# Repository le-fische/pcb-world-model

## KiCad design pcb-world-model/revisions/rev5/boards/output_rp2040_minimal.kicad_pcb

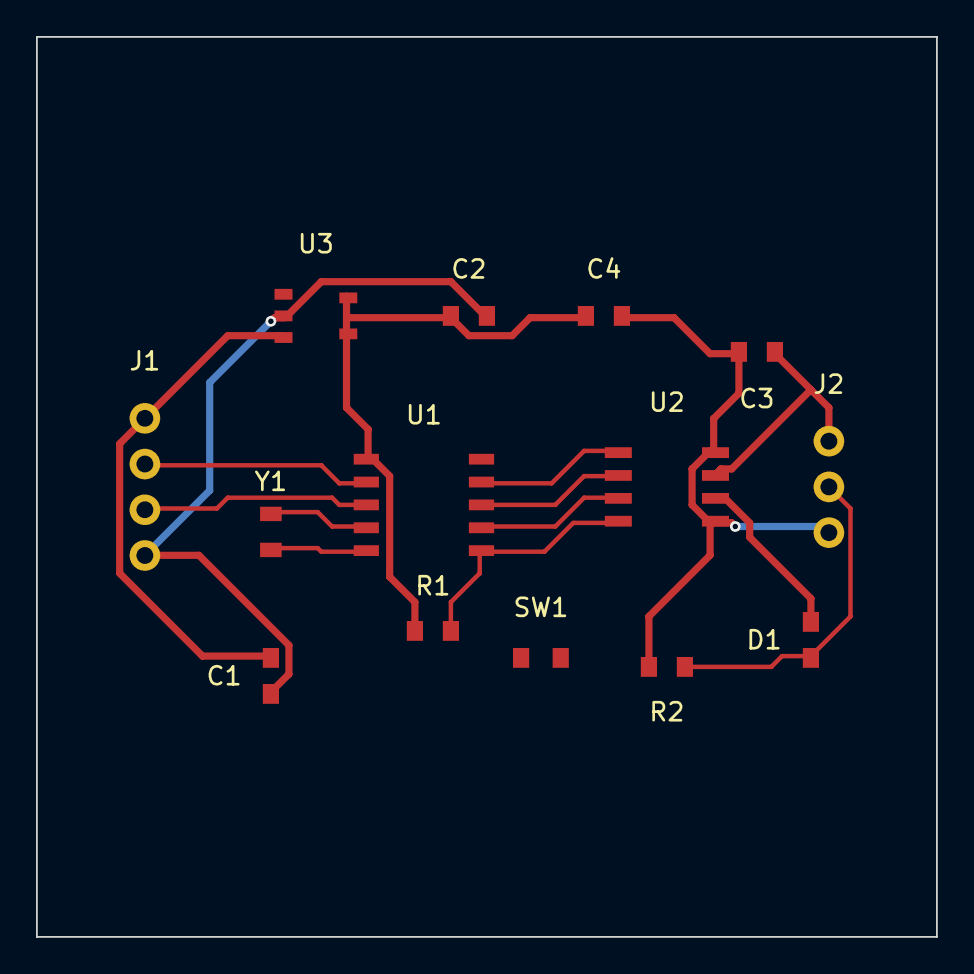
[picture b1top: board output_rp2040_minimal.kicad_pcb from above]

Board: 2 copper layers, 50.0 x 50.0 mm, 14 parts (0 on the bottom side), 12 nets.

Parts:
C1: 10uF_VBUS; C_0805_2012Metric
C2: 100nF_VDD; C_0805_2012Metric
C3: 100nF_CORE; C_0805_2012Metric
C4: 100nF_FLASH; C_0805_2012Metric
D1: PWR_LED; LED_0805_2012Metric
J1: USB_C; USB_C_Receptacle_GCT_USB4085
J2: GPIO_HDR; PinHeader_1x03_P2.54mm_Vertical
R1: 10k_CS; R_0603_1608Metric
R2: 1k_LED; R_0603_1608Metric
SW1: BOOTSEL; SW_SPST_TL3342
U1: RP2040; QFN-10_RP2040_Core
U2: W25Q16JV; SOIC-8_3.9x4.9mm_P1.27mm
U3: NCP1117-3.3; SOT-23-5
Y1: 12MHz; Crystal_SMD_3225

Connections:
GND: C1.2, C2.2, C3.2, C4.2, J1.4, J2.3, R2.2, SW1.2, U2.5, U2.8, U3.2
LED_STAT: D1.2, J2.2, R2.1, U1.6
QSPI_CLK: U1.9, U2.3
QSPI_CS: R1.2, SW1.1, U1.10, U2.4
QSPI_D0: U1.8, U2.2
QSPI_D1: U1.7, U2.1
USB_DM: J1.2, U1.2
USB_DP: J1.3, U1.3
VBUS_5V: C1.1, J1.1, U3.1, U3.3
VCC_3V3: C2.1, C3.1, C4.1, D1.1, J2.1, R1.1, U1.1, U2.6, U2.7, U3.4, U3.5
XIN: U1.4, Y1.1
XOUT: U1.5, Y1.2

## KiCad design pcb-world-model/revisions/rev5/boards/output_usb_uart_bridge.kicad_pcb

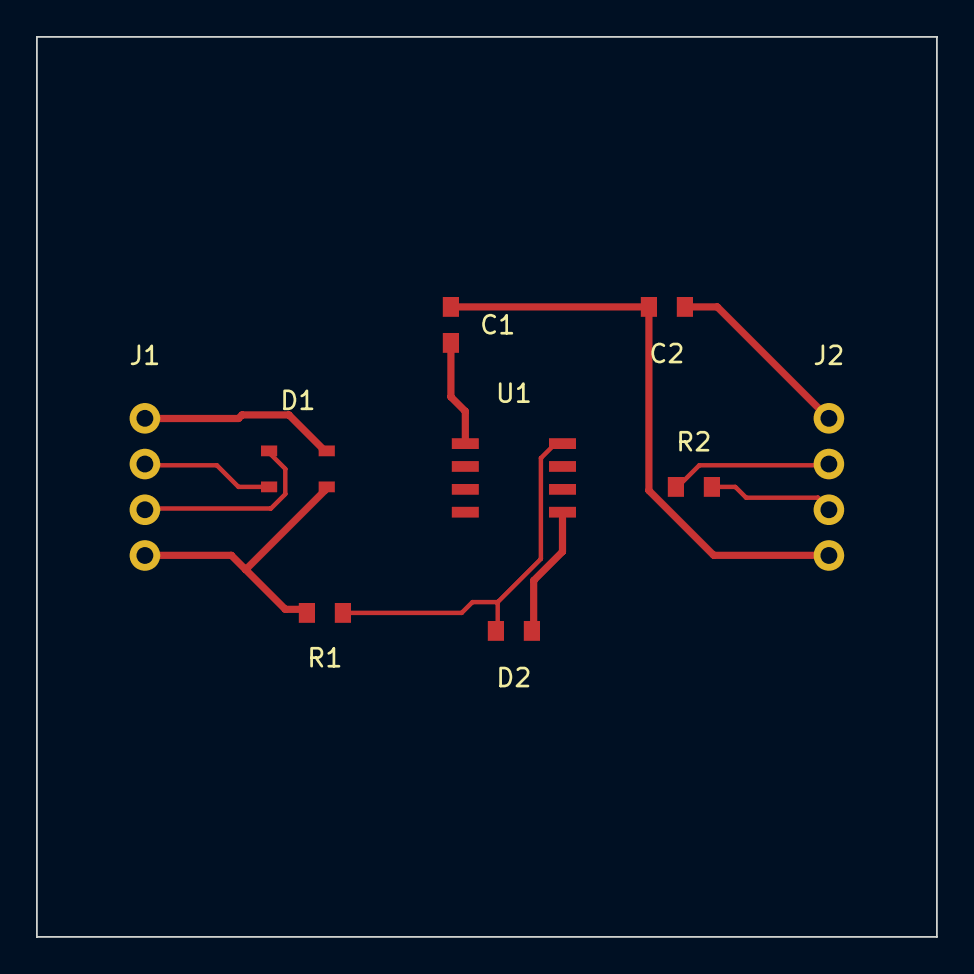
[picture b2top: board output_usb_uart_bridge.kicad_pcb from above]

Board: 2 copper layers, 50.0 x 50.0 mm, 9 parts (0 on the bottom side), 8 nets.

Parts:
C1: 10uF; C_0805_2012Metric
C2: 100nF; C_0805_2012Metric
D1: USBLC6-2SC6; SOT-23-6
D2: TX_LED; LED_0805_2012Metric
J1: USB_PORT; USB_Micro-B_Molex
J2: UART_HDR; PinHeader_1x04_P2.54mm_Vertical
R1: 470R; R_0603_1608Metric
R2: 0R_LOOP_OPT; R_0603_1608Metric
U1: CH340N_BRIDGE; SOIC-8_3.9x4.9mm_P1.27mm

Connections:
GND: C1.2, C2.2, D1.3, J1.4, J2.4, R1.2, U1.4
LED_ACT: D2.2, R1.1, U1.8
UART_RX: J2.3, R2.2, U1.7
UART_TX: J2.2, R2.1, U1.6
USB_DM: D1.2, J1.2, U1.3
USB_DP: D1.1, J1.3, U1.2
VBUS_5V: C1.1, D1.4, J1.1, U1.1
VCC_3V3: C2.1, D2.1, J2.1, U1.5

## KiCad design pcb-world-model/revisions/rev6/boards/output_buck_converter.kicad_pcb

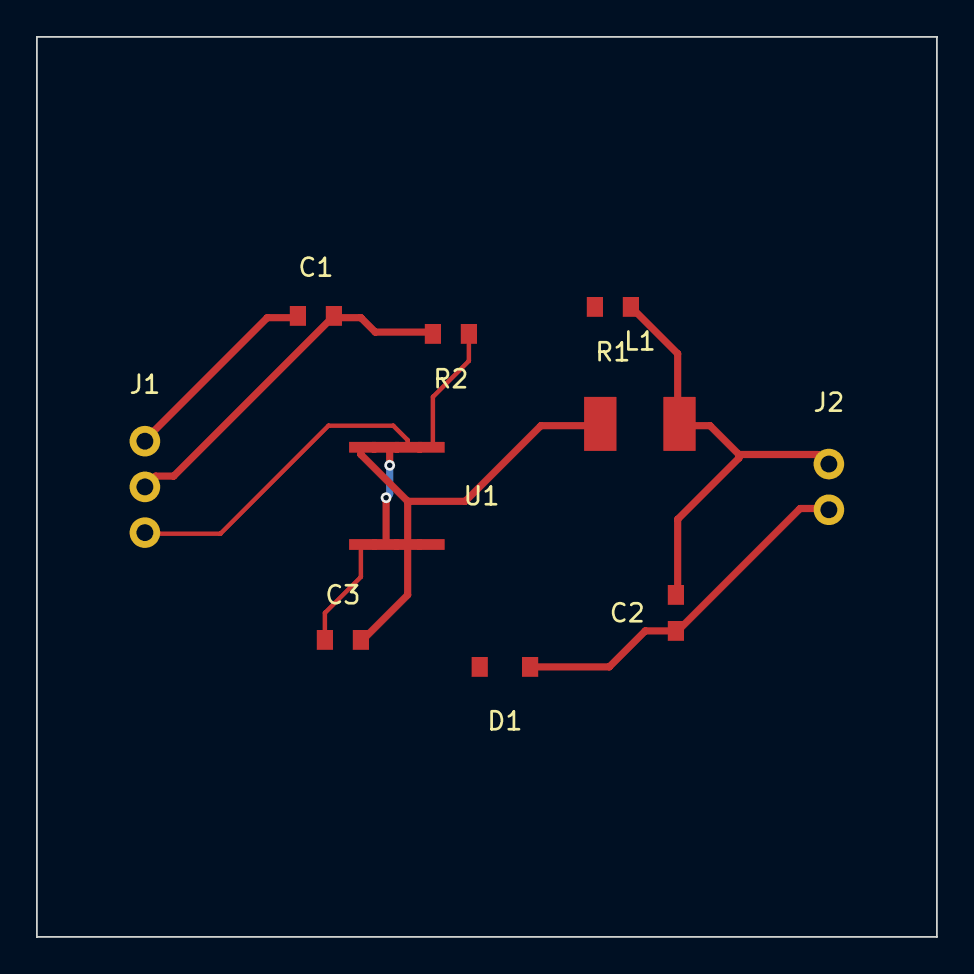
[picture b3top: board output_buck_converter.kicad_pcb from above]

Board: 2 copper layers, 50.0 x 50.0 mm, 10 parts (0 on the bottom side), 7 nets.

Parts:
C1: 22uF_IN; C_1206_3216Metric
C2: 47uF_OUT; C_1206_3216Metric
C3: 100nF_BST; C_0603_1608Metric
D1: SS34; D_SMA
J1: VIN_12V; TerminalBlock_bornier-3_P5.08mm
J2: VOUT_5V; TerminalBlock_bornier-2_P5.08mm
L1: 10uH; L_6.3x6.3_H3
R1: 100k; R_0603_1608Metric
R2: 18.7k; R_0603_1608Metric
U1: TPS54302; SOIC-8_3.9x4.9mm_P1.27mm

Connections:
BOOT: C3.1, U1.1
EN_CTRL: J1.3, U1.6
FB_DIV: R1.2, R2.1, U1.5
GND: C1.2, C2.2, D1.1, J1.2, J2.2, R2.2, U1.4
SW_NODE: C3.2, D1.2, L1.1, U1.3, U1.8
VIN_12V: C1.1, J1.1, U1.2, U1.7
VOUT_5V: C2.1, J2.1, L1.2, R1.1

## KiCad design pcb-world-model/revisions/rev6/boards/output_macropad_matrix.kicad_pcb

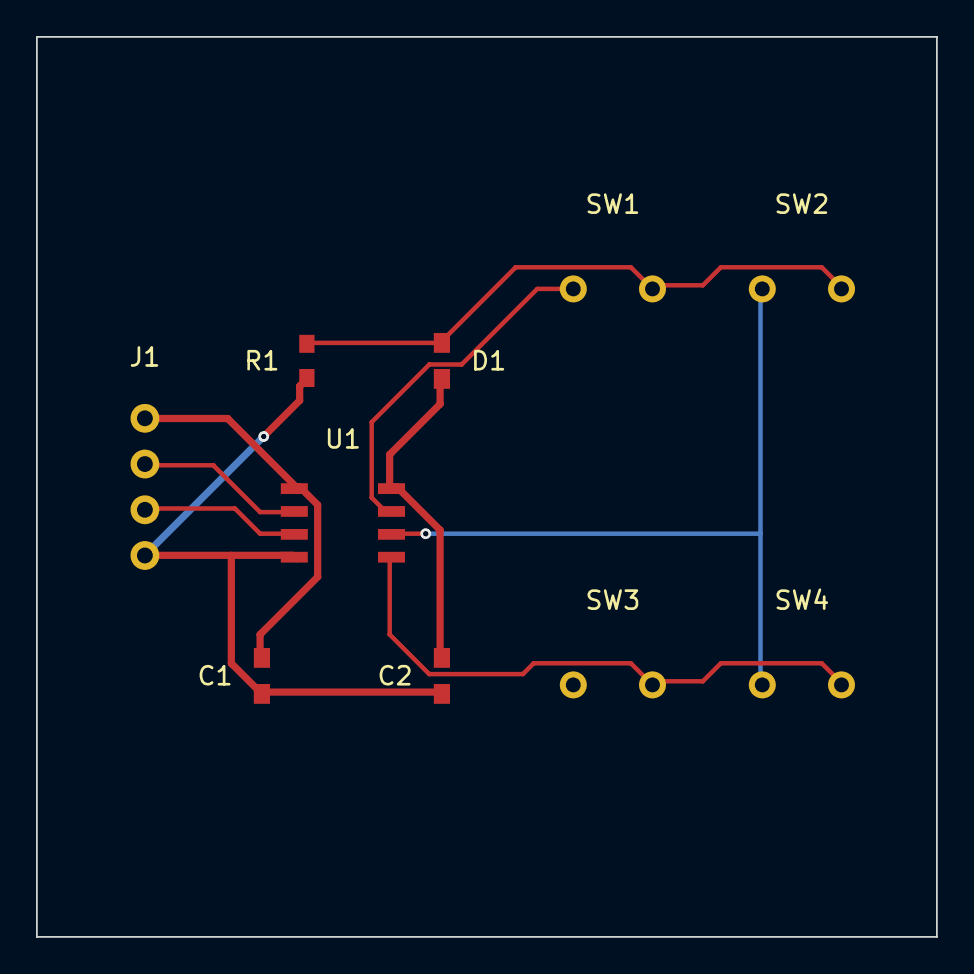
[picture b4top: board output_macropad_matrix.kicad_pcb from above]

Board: 2 copper layers, 50.0 x 50.0 mm, 10 parts (0 on the bottom side), 9 nets.

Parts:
C1: 10uF_VBUS; C_0805_2012Metric
C2: 100nF_VDD; C_0805_2012Metric
D1: ROW0_SCAN; LED_0805_2012Metric
J1: USB_HID_HDR; PinHeader_1x04_P2.54mm
R1: 10k_ROW0; R_0603_1608Metric
SW1: KEY_1; SW_Cherry_MX_1.00u_PCB
SW2: KEY_2; SW_Cherry_MX_1.00u_PCB
SW3: KEY_3; SW_Cherry_MX_1.00u_PCB
SW4: KEY_4; SW_Cherry_MX_1.00u_PCB
U1: CH552G_HID; SOIC-8_3.9x4.9mm_P1.27mm

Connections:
COL0: SW1.1, SW3.1, U1.7
COL1: SW2.1, SW4.1, U1.6
GND: C1.2, C2.2, J1.4, R1.2, U1.4
ROW0: D1.2, R1.1, SW1.2, SW2.2
ROW1: SW3.2, SW4.2, U1.5
USB_DM: J1.2, U1.2
USB_DP: J1.3, U1.3
VBUS_5V: C1.1, J1.1, U1.1
VCC_3V3: C2.1, D1.1, U1.8

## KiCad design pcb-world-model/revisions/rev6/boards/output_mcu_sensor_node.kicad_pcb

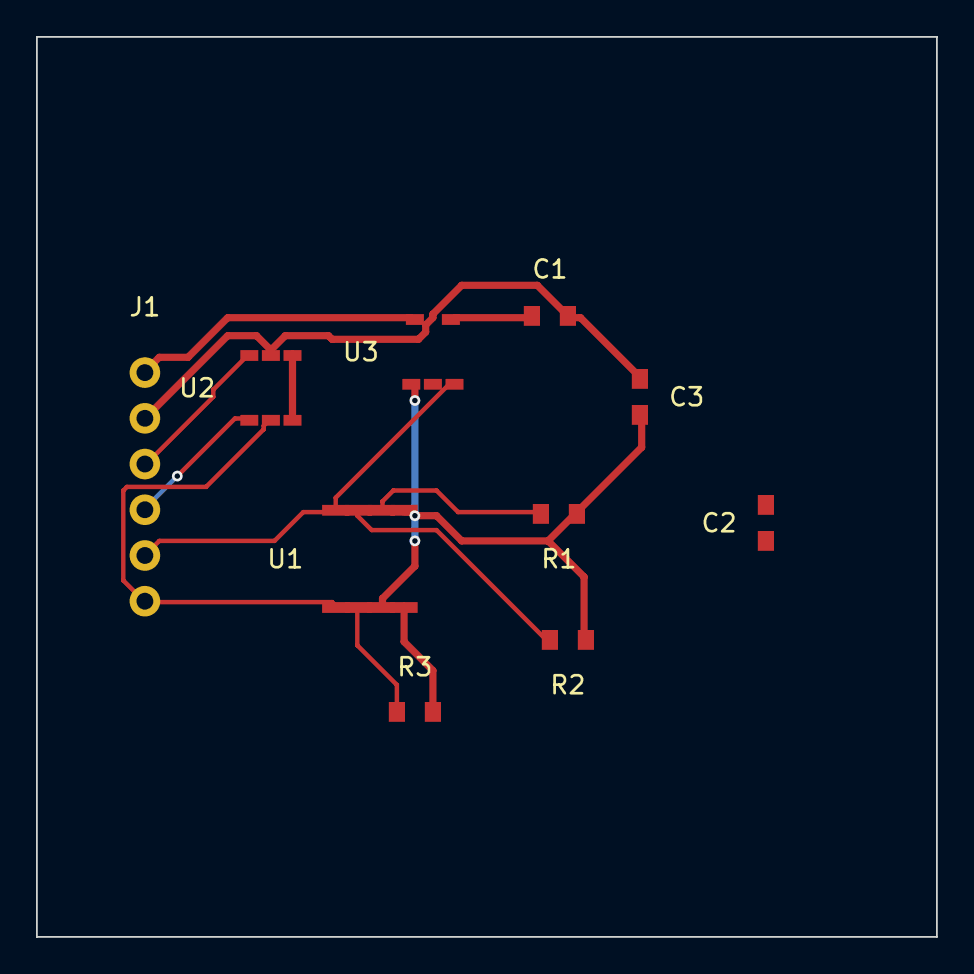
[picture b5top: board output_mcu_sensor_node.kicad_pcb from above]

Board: 2 copper layers, 50.0 x 50.0 mm, 10 parts (0 on the bottom side), 8 nets.

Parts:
C1: 10uF; C_0805_2012Metric
C2, C3: 100nF; C_0805_2012Metric
J1: I2C_HOST_HDR; PinHeader_1x06_P2.54mm_Vertical
R1, R2: 4.7k; R_0603_1608Metric
R3: 1k_LED; R_0603_1608Metric
U1: ATtiny1614; SOIC-8_3.9x4.9mm_P1.27mm
U2: BME280_I2C; SOT-23-6
U3: AP2112K-3.3; SOT-23-5

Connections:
GND: C1.2, C2.2, C3.2, J1.2, R3.2, U1.8, U2.2, U3.2
I2C_SCL: J1.4, R2.2, U1.3, U2.4
I2C_SDA: J1.3, R1.2, U1.2, U2.3
MCU_RST: J1.5, U1.4, U3.5
SENSOR_INT: J1.6, U1.5, U2.5
STATUS_LED: R3.1, U1.6
VCC_3V3: C2.1, C3.1, R1.1, R2.1, U1.1, U1.7, U2.1, U2.6, U3.4
VIN_5V: C1.1, J1.1, U3.1, U3.3

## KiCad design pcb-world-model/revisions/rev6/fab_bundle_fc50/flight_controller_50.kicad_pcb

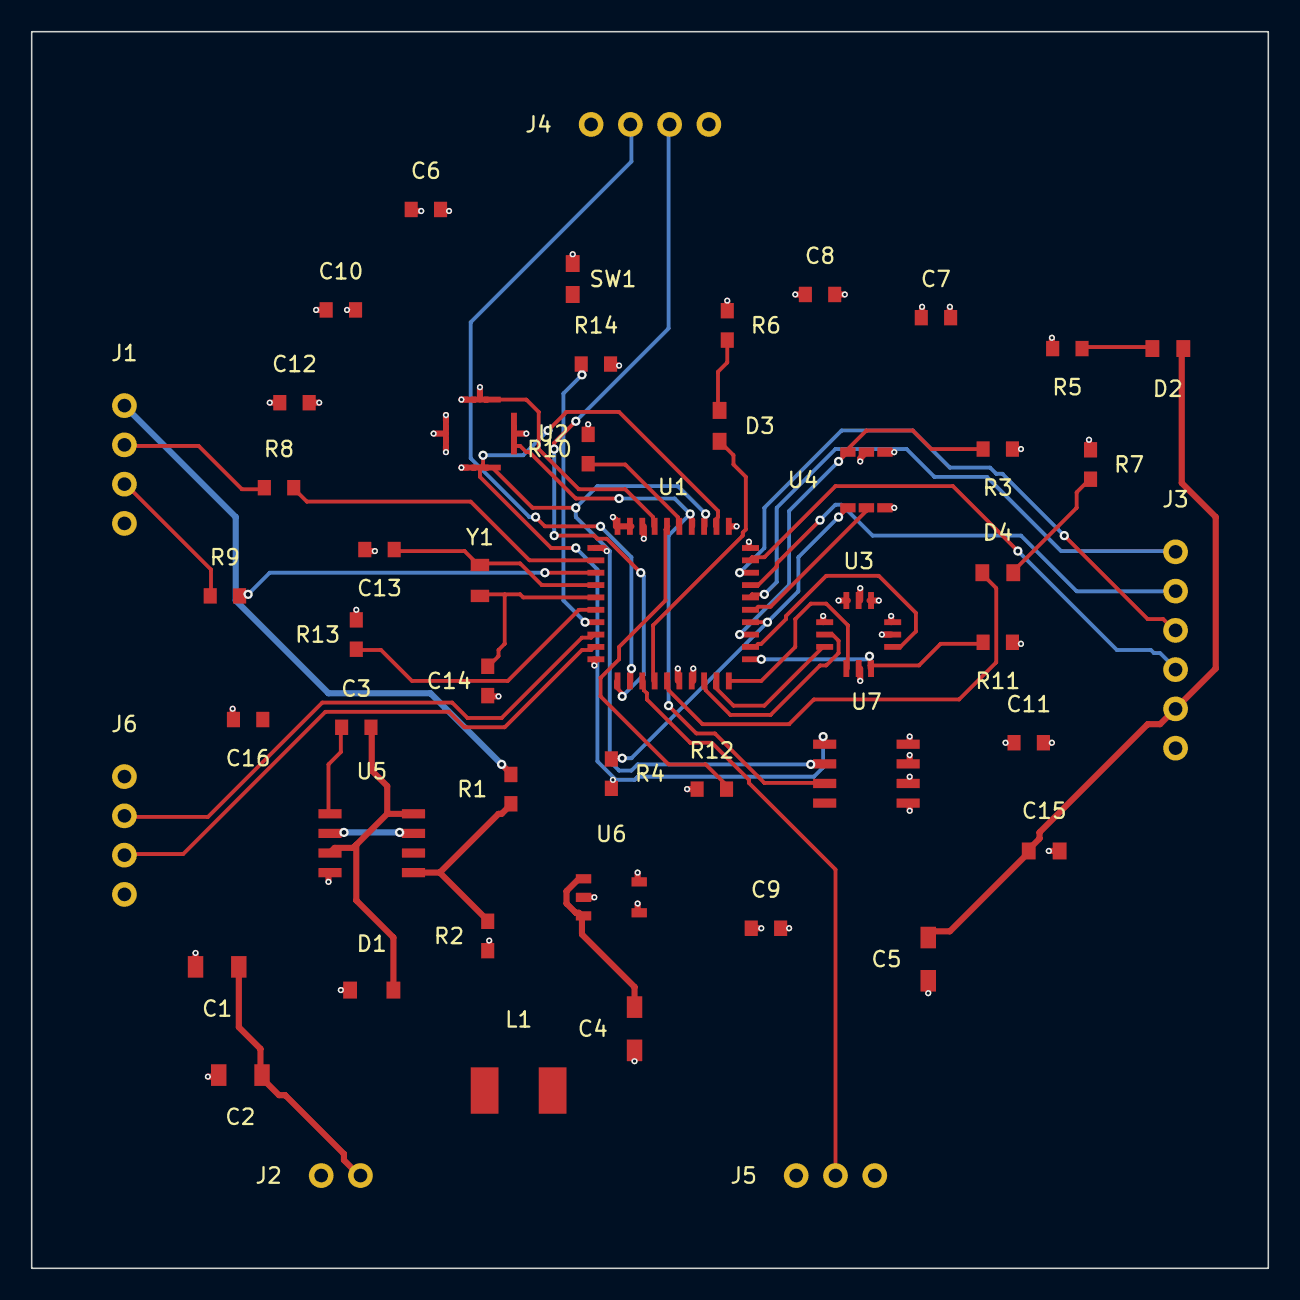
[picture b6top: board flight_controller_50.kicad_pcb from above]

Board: 4 copper layers, 80.0 x 80.0 mm, 50 parts (0 on the bottom side), 43 nets.

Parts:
C1: 22uF_VBAT1; C_1206_3216Metric
C2: 22uF_VBAT2; C_1206_3216Metric
C3: 100nF_BST; C_0603_1608Metric
C4: 47uF_5V1; C_1206_3216Metric
C5: 47uF_5V2; C_1206_3216Metric
C6: 100nF_MCU1; C_0603_1608Metric
C7: 100nF_MCU2; C_0603_1608Metric
C8: 100nF_MCU3; C_0603_1608Metric
C9: 100nF_MCU4; C_0603_1608Metric
C10: 100nF_IMU1; C_0603_1608Metric
C11: 100nF_IMU2; C_0603_1608Metric
C12: 100nF_FLASH; C_0603_1608Metric
C13: 18pF_HSE1; C_0603_1608Metric
C14: 18pF_HSE2; C_0603_1608Metric
C15: 10uF_5V_IN; C_0805_2012Metric
C16: 100nF_NRST; C_0603_1608Metric
D1: SS34_SCHOTTKY; D_SMA
D2: PWR_LED_5V; LED_0805_2012Metric
D3: ARM_LED; LED_0805_2012Metric
D4: GYRO_LED; LED_0805_2012Metric
J1: USB_C_PWR; PinHeader_1x04_P2.54mm
J2: VBAT_16V_IN; PinHeader_1x02_P2.54mm
J3: ESC_PWM_1_4; PinHeader_1x06_P2.54mm
J4: GPS_UART1; PinHeader_1x04_P2.54mm
J5: RC_SBUS_RX; PinHeader_1x03_P2.54mm
J6: SWD_DEBUG; PinHeader_1x04_P2.54mm
L1: 10uH_BUCK; L_6.3x6.3_H3
R1: 100k_FB; R_0603_1608Metric
R2: 18.7k_FB; R_0603_1608Metric
R3: 4.7k_SDA; R_0603_1608Metric
R4: 4.7k_SCL; R_0603_1608Metric
R5: 1k_PWR_LED; R_0603_1608Metric
R6: 1k_ARM_LED; R_0603_1608Metric
R7: 1k_GYRO_LED; R_0603_1608Metric
R8: 22R_USB_DP; R_0603_1608Metric
R9: 22R_USB_DM; R_0603_1608Metric
R10: 10k_CS_IMU1; R_0603_1608Metric
R11: 10k_CS_IMU2; R_0603_1608Metric
R12: 10k_CS_FLS; R_0603_1608Metric
R13: 10k_NRST; R_0603_1608Metric
R14: 10k_BOOT0; R_0603_1608Metric
SW1: BOOT0_BTN; SMD_0805_2012Metric
U1: STM32F405_FC; QFN-40_7.0x7.0mm_P0.8mm
U2: ICM42688P_IMU1; QFN-12_4.0x4.0mm_P0.8mm
U3: BMI270_IMU2; QFN-12_4.0x4.0mm_P0.8mm
U4: BMP388_BARO; SOT-23-6
U5: TPS54302_5V; SOIC-8_3.9x4.9mm_P1.27mm
U6: AP2112K_3V3; SOT-23-5
U7: W25Q128_FLASH; SOIC-8_3.9x4.9mm_P1.27mm
Y1: 16MHz_HSE; Crystal_SMD_3225

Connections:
ARM_LED_SIG: D3.1, U1.14
BARO_INT: U1.25, U4.5
BOOT_SW: C3.1, U5.1
FB_5V: R1.2, R2.1, U5.5
GND: C1.2, C2.2, C4.2, C5.2, C6.2, C7.2, C8.2, C9.2, C10.2, C11.2, C12.2, C13.2, C14.2, C15.2, C16.2, D1.1, J1.4, J2.2, J3.6, J4.4, J5.3, J6.4, R2.2, R5.2, R6.2, R7.2, R14.2, SW1.2, U1.10, U1.17, U1.30, U1.39, U1.40, U2.5, U2.9, U2.11, U3.5, U3.9, U3.11, U4.2, U5.4, U6.2, U7.7, U7.8
GYRO_LED_SIG: D4.1, U1.15
HSE_IN: C13.1, U1.4, Y1.1
HSE_OUT: C14.1, U1.5, Y1.2
I2C1_SCL: R4.2, U1.24, U4.4
I2C1_SDA: R3.2, U1.23, U4.3
IMU1_INT: U1.37, U2.7
IMU2_INT: U1.22, U3.7
LED2_K: D2.2, R5.1
LED3_K: D3.2, R6.1
LED4_K: D4.2, R7.1
M1_PWM: J3.1, U1.26
M2_PWM: J3.2, U1.27
M3_PWM: J3.3, U1.28
M4_PWM: J3.4, U1.29
MCU_BOOT: R14.1, SW1.1, U1.7
MCU_NRST: C16.1, R13.2, U1.6
RC_SBUS: J5.2, U1.13
SPI1_CS_FLASH: R12.2, U1.36, U7.4
SPI1_CS_IMU1: R10.2, U1.35, U2.6
SPI1_MISO: U1.34, U2.4, U7.3
SPI1_MOSI: U1.33, U2.3, U7.2
SPI1_SCK: U1.32, U2.2, U7.1
SPI2_CS_IMU2: R11.2, U1.21, U3.6
SPI2_MISO: U1.20, U3.4
SPI2_MOSI: U1.19, U3.3
SPI2_SCK: U1.18, U3.2
SWCLK: J6.3, U1.9
SWDIO: J6.2, U1.8
SW_NODE: C3.2, D1.2, L1.1, U5.3, U5.8
UART1_RX: J4.3, U1.12
UART1_TX: J4.2, U1.11
USB_DM: J1.3, R9.1
USB_DM_MCU: R9.2, U1.3
USB_DP: J1.2, R8.1
USB_DP_MCU: R8.2, U1.2
VBAT_16V: C1.1, C2.1, J2.1, U5.2, U5.6, U5.7
VCC_3V3: C6.1, C7.1, C8.1, C9.1, C10.1, C11.1, C12.1, J4.1, J5.1, J6.1, R3.1, R4.1, R10.1, R11.1, R12.1, R13.1, U1.1, U1.16, U1.31, U1.38, U2.1, U2.8, U2.10, U2.12, U3.1, U3.8, U3.10, U3.12, U4.1, U4.6, U6.4, U6.5, U7.5, U7.6
VCC_5V: C4.1, C5.1, C15.1, D2.1, J1.1, J3.5, L1.2, R1.1, U6.1, U6.3

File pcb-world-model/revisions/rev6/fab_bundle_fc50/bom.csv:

Comment,Designator,Footprint,Quantity
22uF_VBAT1,C1,Capacitor_SMD:C_1206_3216Metric,1
100nF_IMU1,C10,Capacitor_SMD:C_0603_1608Metric,1
100nF_IMU2,C11,Capacitor_SMD:C_0603_1608Metric,1
100nF_FLASH,C12,Capacitor_SMD:C_0603_1608Metric,1
18pF_HSE1,C13,Capacitor_SMD:C_0603_1608Metric,1
18pF_HSE2,C14,Capacitor_SMD:C_0603_1608Metric,1
10uF_5V_IN,C15,Capacitor_SMD:C_0805_2012Metric,1
100nF_NRST,C16,Capacitor_SMD:C_0603_1608Metric,1
22uF_VBAT2,C2,Capacitor_SMD:C_1206_3216Metric,1
100nF_BST,C3,Capacitor_SMD:C_0603_1608Metric,1
47uF_5V1,C4,Capacitor_SMD:C_1206_3216Metric,1
47uF_5V2,C5,Capacitor_SMD:C_1206_3216Metric,1
100nF_MCU1,C6,Capacitor_SMD:C_0603_1608Metric,1
100nF_MCU2,C7,Capacitor_SMD:C_0603_1608Metric,1
100nF_MCU3,C8,Capacitor_SMD:C_0603_1608Metric,1
100nF_MCU4,C9,Capacitor_SMD:C_0603_1608Metric,1
SS34_SCHOTTKY,D1,Diode_SMD:D_SMA,1
PWR_LED_5V,D2,LED_SMD:LED_0805_2012Metric,1
ARM_LED,D3,LED_SMD:LED_0805_2012Metric,1
GYRO_LED,D4,LED_SMD:LED_0805_2012Metric,1
USB_C_PWR,J1,Connector_PinHeader_2.54mm:PinHeader_1x04_P2.54mm,1
VBAT_16V_IN,J2,Connector_PinHeader_2.54mm:PinHeader_1x02_P2.54mm,1
ESC_PWM_1_4,J3,Connector_PinHeader_2.54mm:PinHeader_1x06_P2.54mm,1
GPS_UART1,J4,Connector_PinHeader_2.54mm:PinHeader_1x04_P2.54mm,1
RC_SBUS_RX,J5,Connector_PinHeader_2.54mm:PinHeader_1x03_P2.54mm,1
SWD_DEBUG,J6,Connector_PinHeader_2.54mm:PinHeader_1x04_P2.54mm,1
10uH_BUCK,L1,Inductor_SMD:L_6.3x6.3_H3,1
100k_FB,R1,Resistor_SMD:R_0603_1608Metric,1
10k_CS_IMU1,R10,Resistor_SMD:R_0603_1608Metric,1
10k_CS_IMU2,R11,Resistor_SMD:R_0603_1608Metric,1
10k_CS_FLS,R12,Resistor_SMD:R_0603_1608Metric,1
10k_NRST,R13,Resistor_SMD:R_0603_1608Metric,1
10k_BOOT0,R14,Resistor_SMD:R_0603_1608Metric,1
18.7k_FB,R2,Resistor_SMD:R_0603_1608Metric,1
4.7k_SDA,R3,Resistor_SMD:R_0603_1608Metric,1
4.7k_SCL,R4,Resistor_SMD:R_0603_1608Metric,1
1k_PWR_LED,R5,Resistor_SMD:R_0603_1608Metric,1
1k_ARM_LED,R6,Resistor_SMD:R_0603_1608Metric,1
1k_GYRO_LED,R7,Resistor_SMD:R_0603_1608Metric,1
22R_USB_DP,R8,Resistor_SMD:R_0603_1608Metric,1
22R_USB_DM,R9,Resistor_SMD:R_0603_1608Metric,1
BOOT0_BTN,SW1,Package_SMD:SMD_0805_2012Metric,1
STM32F405_FC,U1,Package_DFN_QFN:QFN-40_7.0x7.0mm_P0.8mm,1
ICM42688P_IMU1,U2,Package_DFN_QFN:QFN-12_4.0x4.0mm_P0.8mm,1
BMI270_IMU2,U3,Package_DFN_QFN:QFN-12_4.0x4.0mm_P0.8mm,1
BMP388_BARO,U4,Package_TO_SOT_SMD:SOT-23-6,1
TPS54302_5V,U5,Package_SO:SOIC-8_3.9x4.9mm_P1.27mm,1
AP2112K_3V3,U6,Package_TO_SOT_SMD:SOT-23-5,1
W25Q128_FLASH,U7,Package_SO:SOIC-8_3.9x4.9mm_P1.27mm,1
16MHz_HSE,Y1,Crystal:Crystal_SMD_3225,1

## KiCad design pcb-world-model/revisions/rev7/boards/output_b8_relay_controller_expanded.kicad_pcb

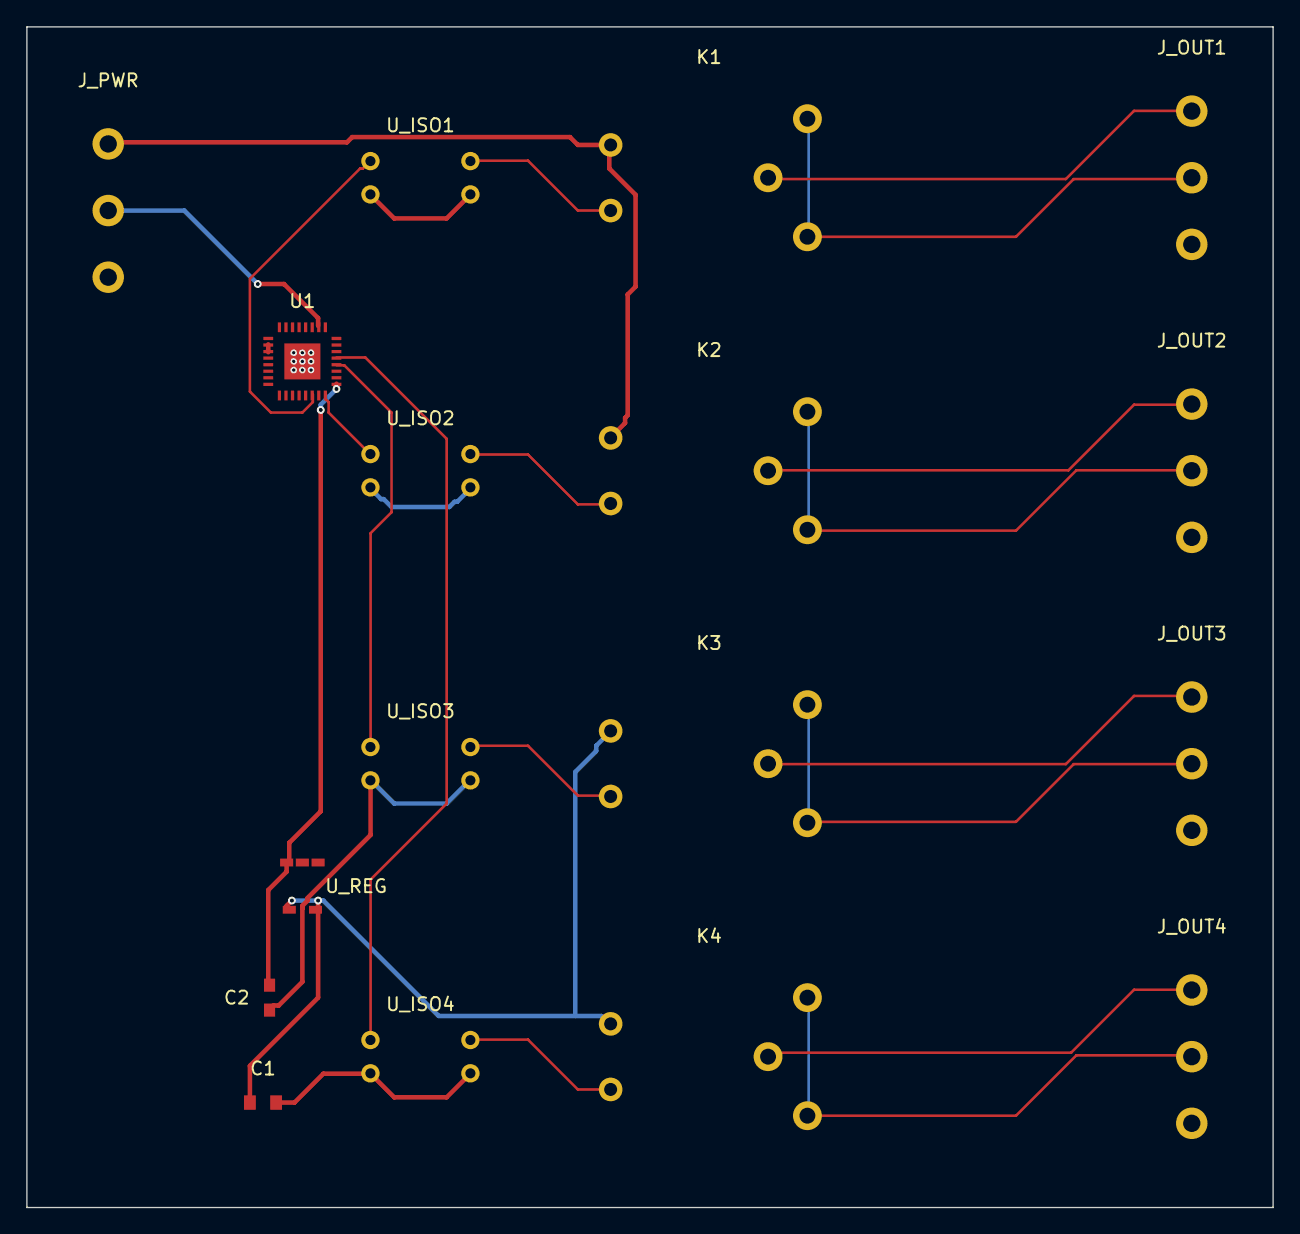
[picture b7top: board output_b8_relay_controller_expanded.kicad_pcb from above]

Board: 2 copper layers, 95.0 x 90.0 mm, 17 parts (0 on the bottom side), 19 nets.

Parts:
C1: 10uF_5V; C_0805_2012Metric
C2: 100nF_3V3; C_0603_1608Metric
J_OUT1, J_OUT2, J_OUT3, J_OUT4: ScrewTerminal_5.08mm; TerminalBlock_Phoenix_MKDS_1,5-3-5.08_1x03_P5.08mm_Horizont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
J_PWR: ScrewTerminal_5.08mm; TerminalBlock_Phoenix_MKDS_1,5-3-5.08_1x03_P5.08mm_Horizont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
K1, K2, K3, K4: Relay_SPDT_10A; Relay_SPDT_SANYOU_SRD_Series_Form_C
U1: ESP32-C3FN4; QFN-32_5.0x5.0mm_P0.5mm
U_ISO1, U_ISO2, U_ISO3, U_ISO4: PC817; DIP-4_W7.62mm
U_REG: AP2112K-3.3; SOT-23-5

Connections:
COIL_DRV_1: K1.2, U_ISO1.4
COIL_DRV_2: K2.2, U_ISO2.4
COIL_DRV_3: K3.2, U_ISO3.4
COIL_DRV_4: K4.2, U_ISO4.4
GND: C1.2, C2.2, J_PWR.2, U1.26, U1.33, U_ISO1.2, U_ISO1.3, U_ISO2.2, U_ISO2.3, U_ISO3.2, U_ISO3.3, U_ISO4.2, U_ISO4.3, U_REG.2
HV_COM_1: J_OUT1.1, K1.3
HV_COM_2: J_OUT2.1, K2.3
HV_COM_3: J_OUT3.1, K3.3
HV_COM_4: J_OUT4.1, K4.3
HV_NO_1: J_OUT1.2, K1.4, K1.5
HV_NO_2: J_OUT2.2, K2.4, K2.5
HV_NO_3: J_OUT3.2, K3.4, K3.5
HV_NO_4: J_OUT4.2, K4.4, K4.5
RELAY_CTRL_1: U1.14, U_ISO1.1
RELAY_CTRL_2: U1.16, U_ISO2.1
RELAY_CTRL_3: U1.20, U_ISO3.1
RELAY_CTRL_4: U1.21, U_ISO4.1
VCC_3V3: C2.1, U1.2, U1.3, U1.17, U_REG.5
VIN_5V: C1.1, J_PWR.1, K1.1, K2.1, K3.1, K4.1, U_REG.1, U_REG.3
